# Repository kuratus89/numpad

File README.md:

# numpad

## hackpad

## case

## schematic

## pcb

## BOM

Seeed XIAO RP2040 -1

Through-hole 1N4148 Diodes -9

MX-Style switches -9

EC11 Rotary encoders -1

0.91 inch OLED displays -1

SK6812 MINI-E LEDs -9

M3x16mm screws -8

M3x5mx4mm heatset inserts -8

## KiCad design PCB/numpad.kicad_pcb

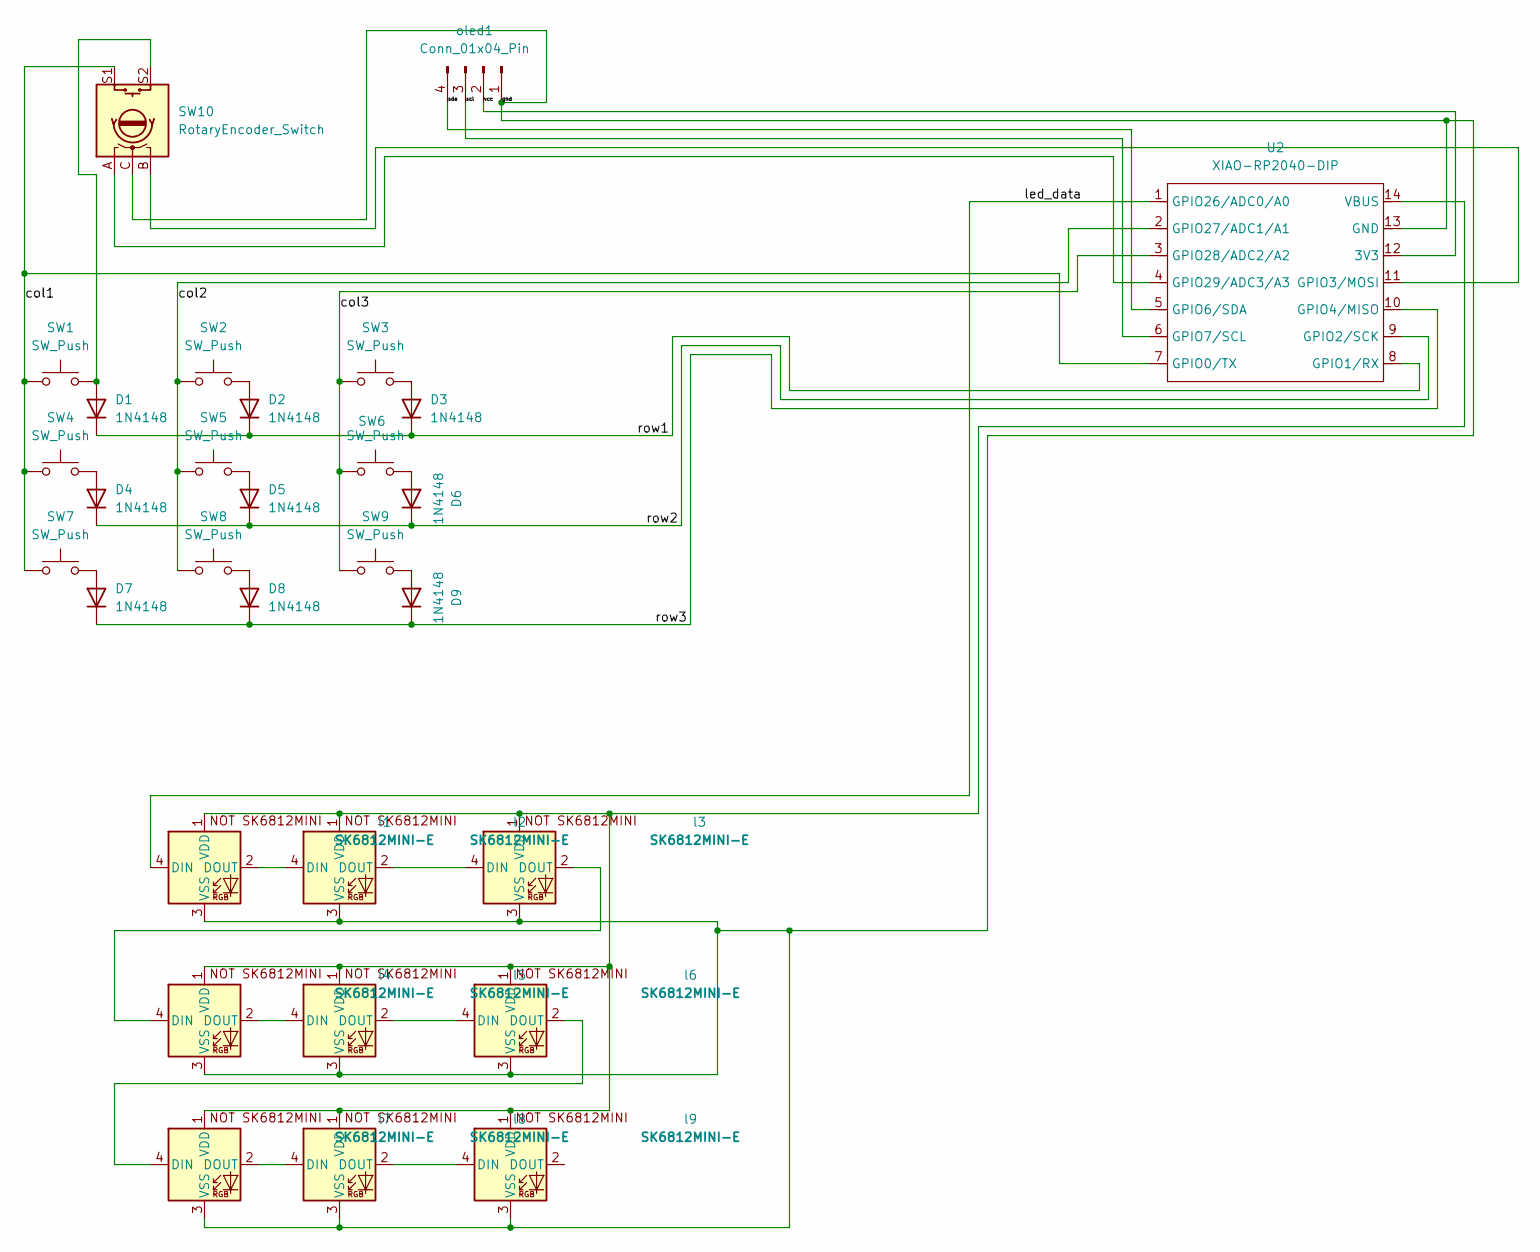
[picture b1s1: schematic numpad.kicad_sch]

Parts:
D1, D2, D3, D4, D5, D6, D7, D8, D9: 1N4148; D_DO-35_SOD27_P7.62mm_Horizontal
SW1, SW2, SW3, SW4, SW5, SW6, SW7, SW8, SW9: SW_Push; SW_Cherry_MX_1.00u_PCB
SW10: RotaryEncoder_Switch; RotaryEncoder_Alps_EC11E-Switch_Vertical_H20mm
U2: XIAO-RP2040-DIP
l1, l2, l3, l4, l5, l6, l7, l8, l9: SK6812MINI-E; MX_SK6812MINI-E_REV
oled1: Conn_01x04_Pin; OLED_0.91_128x32

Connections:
/<NO NET>: U2.6 (GPIO7/SCL), oled1.3
/col1: SW1.1, SW4.1, SW7.1, SW10.S1, U2.7 (GPIO0/TX)
/col2: SW2.1, SW5.1, SW8.1, U2.2 (GPIO27/ADC1/A1)
/col3: SW3.1, SW6.1, SW9.1, U2.3 (GPIO28/ADC2/A2)
/gnd: SW10.C, U2.13 (GND), l1.3 (VSS), l2.3 (VSS), l3.3 (VSS), l4.3 (VSS), l5.3 (VSS), l6.3 (VSS), l7.3 (VSS), l8.3 (VSS), l9.3 (VSS), oled1.1
/led_data: U2.1 (GPIO26/ADC0/A0), l1.4 (DIN)
/row1: D1.1 (K), D2.1 (K), D3.1 (K), U2.8 (GPIO1/RX)
/row2: D4.1 (K), D5.1 (K), D6.1 (K), U2.9 (GPIO2/SCK)
/row3: D7.1 (K), D8.1 (K), D9.1 (K), U2.10 (GPIO4/MISO)
/sda: U2.5 (GPIO6/SDA), oled1.4
/vcc: U2.12 (3V3), oled1.2
unnamed: D1.2 (A), SW1.2, SW10.S2
unnamed: D2.2 (A), SW2.2
unnamed: D3.2 (A), SW3.2
unnamed: D4.2 (A), SW4.2
unnamed: D5.2 (A), SW5.2
unnamed: D6.2 (A), SW6.2
unnamed: D7.2 (A), SW7.2
unnamed: D8.2 (A), SW8.2
unnamed: D9.2 (A), SW9.2
unnamed: SW10.B, U2.11 (GPIO3/MOSI)
unnamed: SW10.A, U2.4 (GPIO29/ADC3/A3)
unnamed: U2.14 (VBUS), l1.1 (VDD), l2.1 (VDD), l3.1 (VDD), l4.1 (VDD), l5.1 (VDD), l6.1 (VDD), l7.1 (VDD), l8.1 (VDD), l9.1 (VDD)
unnamed: l1.2 (DOUT), l2.4 (DIN)
unnamed: l2.2 (DOUT), l3.4 (DIN)
unnamed: l3.2 (DOUT), l4.4 (DIN)
unnamed: l4.2 (DOUT), l5.4 (DIN)
unnamed: l5.2 (DOUT), l6.4 (DIN)
unnamed: l6.2 (DOUT), l7.4 (DIN)
unnamed: l7.2 (DOUT), l8.4 (DIN)
unnamed: l8.2 (DOUT), l9.4 (DIN)

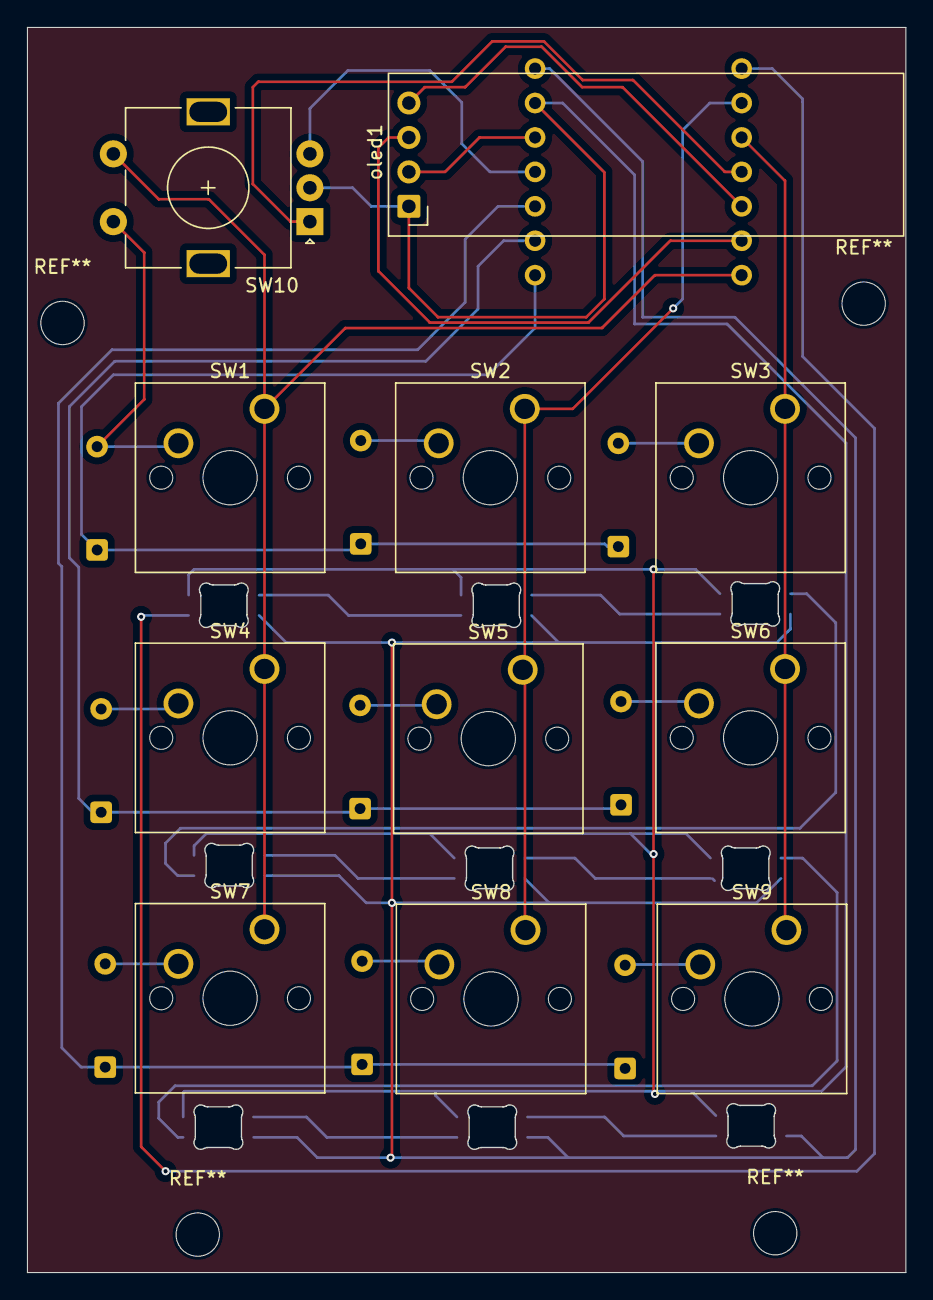
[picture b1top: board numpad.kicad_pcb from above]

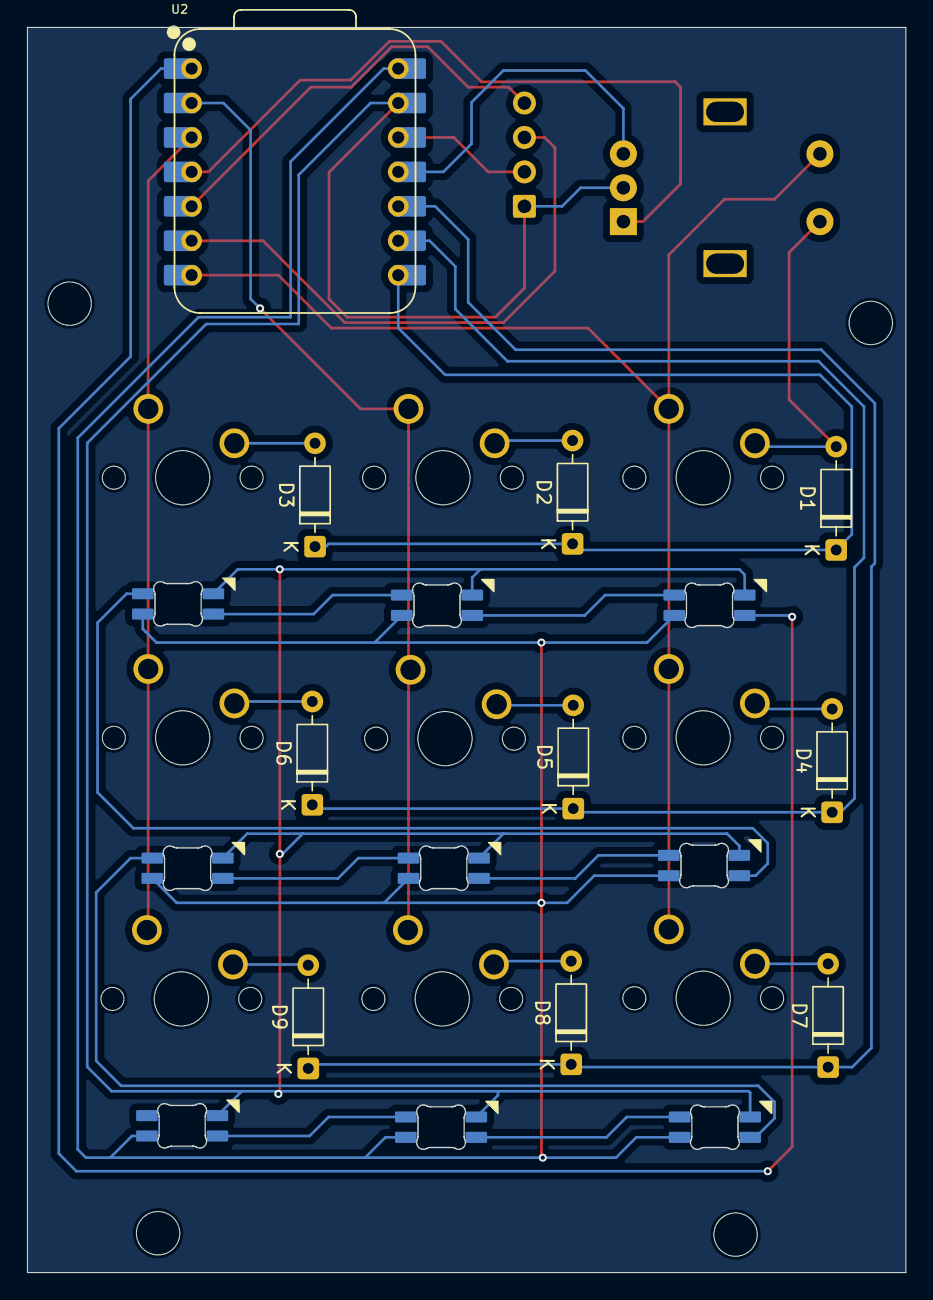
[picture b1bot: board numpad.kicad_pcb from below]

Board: 2 copper layers, 64.8 x 91.8 mm, 30 parts (10 on the bottom side), 31 nets.

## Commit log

2026-01-27 numpad
2026-01-27 Expand README with images and BOM details
    Added detailed sections including images for hackpad, case, schematic, and PCB, along with a Bill of Materials (BOM).
2026-01-28 added step files
